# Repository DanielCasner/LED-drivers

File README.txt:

This repository contains source files for hardware software and simulation for various LED drivers initially created by Daniel Casner, www.danielcasner.org daniel@danielcasner.org

See LICENSE file for details on the licenses pertaining to various files.
Hardware source files are compatible with EAGLE 6.0 http://www.cadsoftusa.com/
Simulation source files are compatible with free LTSpice from Linear Technology http://www.linear.com/ltspice
There is no relationship nor implied endorcement between the author of this work and the above software tools.

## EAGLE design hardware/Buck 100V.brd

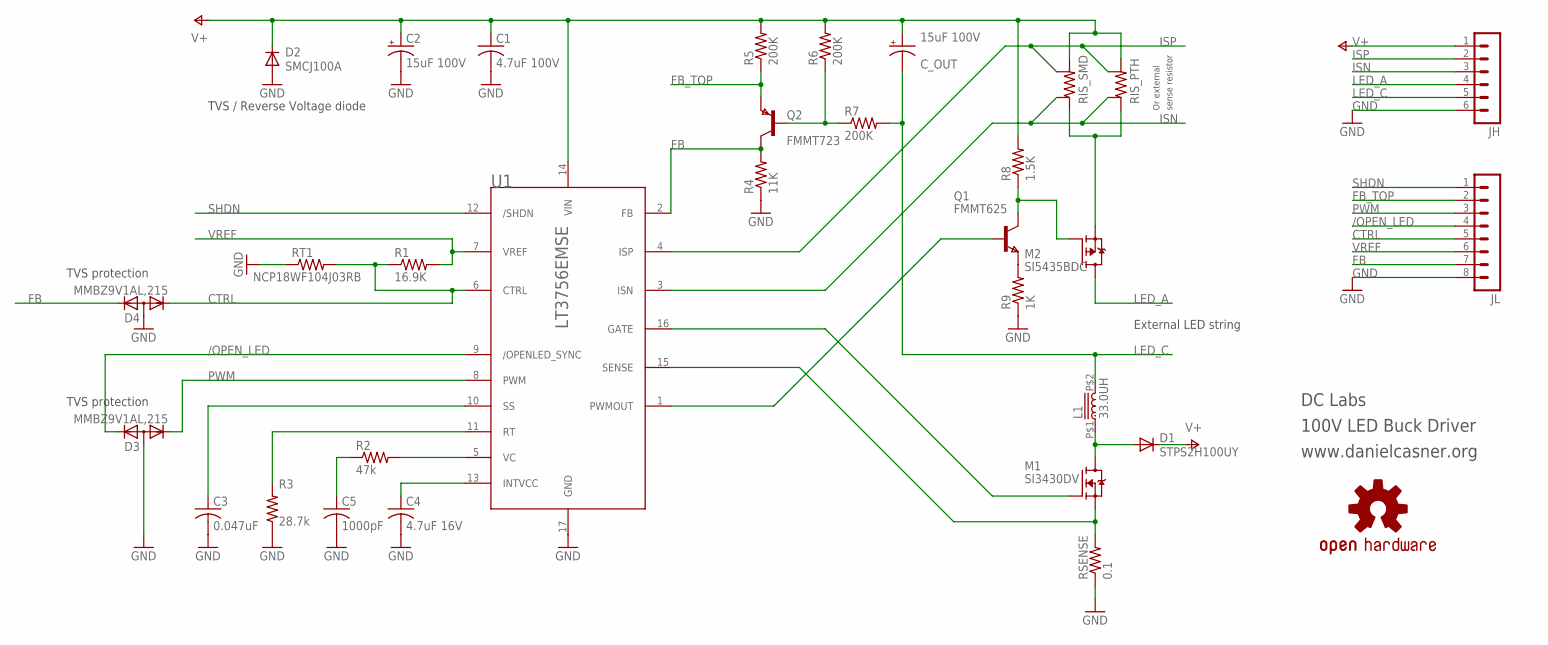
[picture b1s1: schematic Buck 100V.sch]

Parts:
C1: 4.7uF 100V; C2220K
C2: 15uF 100V; E2,5-6E
C3: 0.047uF; C0805
C4: 4.7uF 16V; C0805
C5: 1000pF; C0805
C_OUT: 15uF 100V; E2,5-6E
D1: STPS2H100UY; SMB
D2: SMCJ100A; SMC
D3, D4: MMBZ9V1AL,215; SOT23
JH: MA06-1
JL: MA08-1
L1: 33.0UH; ASPI-0612FS
M1: SI3430DV; SSOT6
M2: SI5435BDC; 1206-8CHIP-FET
Q1: FMMT625; SOT-23
Q2: FMMT723; SOT-23
R1: 16.9K; R0805
R2: 47k; R0805
R3: 28.7k; R0805
R4: 11K; R0805
R5, R6, R7: 200K; R0805
R8: 1.5K; R0805
R9: 1K; R0805
RIS_PTH: R-KELVIN0204/7; 0204/7-KELVIN
RIS_SMD: R-KELVINR2512; R2512_KELVIN
RSENSE: 0.1; R0805
RT1: NCP18WF104J03RB; R0805
U1: LT3756EMSE; MSOP16EXP
U$1: OSHW-LOGOS; OSHW-LOGO-S

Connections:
/OPEN_LED: D3.2 (K2), JL.4, U1.9 (/OPENLED_SYNC)
CTRL: D4.1 (K1), JL.5, R1.1, RT1.2, U1.6 (CTRL)
FB: D4.2 (K2), JL.7, Q2.1 (C), R4.2, U1.2 (FB)
FB_TOP: JL.2, Q2.2 (E), R5.1
GND: C1.2, C2.-, C3.2, C4.2, C5.2, D2.A, D3.3 (A), D4.3 (A), JH.6, JL.8, R3.1, R4.1, R9.1, RSENSE.1, RT1.1, U1.17 (GND)
ISN: JH.3, RIS_PTH.1S, RIS_SMD.1S, U1.3 (ISN)
ISP: JH.2, RIS_PTH.2S, RIS_SMD.2S, U1.4 (ISP)
LED_A: JH.4, M2.1 (D), M2.2 (D), M2.3 (D), M2.6 (D), M2.7 (D), M2.8 (D)
LED_C: C_OUT.-, JH.5, L1.P$2 (2), R7.2
unnamed: C3.1, U1.10 (SS)
unnamed: C4.1, U1.13 (INTVCC)
unnamed: R2.2, U1.5 (VC)
unnamed: C5.1, R2.1
unnamed: R3.2, U1.11 (RT)
unnamed: M2.5 (S), RIS_PTH.1, RIS_SMD.1
unnamed: Q2.3 (B), R6.1, R7.1
unnamed: M2.4 (G), Q1.1 (C), R8.1
unnamed: Q1.2 (E), R9.2
unnamed: Q1.3 (B), U1.1 (PWMOUT)
unnamed: M1.3 (G), U1.16 (GATE)
unnamed: M1.4 (S), RSENSE.2, U1.15 (SENSE)
N_BUCK: D1.A, L1.P$1 (1), M1.1 (D), M1.2 (D), M1.5 (D), M1.6 (D)
PWM: D3.1 (K1), JL.3, U1.8 (PWM)
SHDN: JL.1, U1.12 (/SHDN)
V+: C1.1, C2.+, C_OUT.+, D1.C, D2.C, JH.1, R5.2, R6.2, R8.2, RIS_PTH.2, RIS_SMD.2, U1.14 (VIN)
VREF: JL.6, R1.2, U1.7 (VREF)

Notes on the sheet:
TVS / Reverse Voltage diode
TVS protection
Or external
sense resistor
External LED string
DC Labs
100V LED Buck Driver
www.danielcasner.org

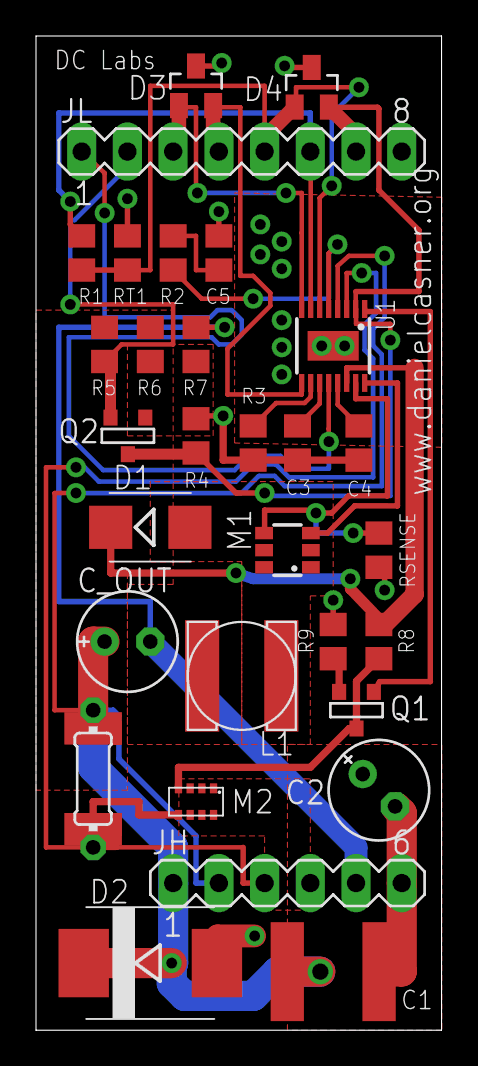
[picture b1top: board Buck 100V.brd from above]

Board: 2 copper layers, 22.5 x 55.2 mm, 32 parts (1 on the bottom side), 26 nets.

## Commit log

2012-03-02 Initialization commit
2012-03-02 Add simulation source files.
2012-03-03 Add license file, add content to readme file and rename to add .txt for windows users.
2012-03-03 Checkpoint, added EAGLE Library and start buck schematic.
2012-03-12 More progress on schematic.
2012-03-13 More work on Buck schematic. Now it just needs the schotkey diode, headers and double checking.
2012-03-14 Add schottky diode. Change resistors and caps to 0805 for hand solderability. Still need headers and checking before starting layout. Also need reverse protection diode and possibly est protection co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
2012-03-15 Finished schematic (needs a careful double check). Added LTSpice output files to .gitignore.
2012-03-15 Beautify and correct the schematic. Made the two headers different sizes so that it is harder to put the part in backwards. Next step is to run and confirm BOM.
2012-03-17 Minor fixes.
2012-03-17 Add BOM spread sheet for Buck driver.
2012-03-17 Add board created from schematic. No placement done yet.
2012-03-21 Create kelvin terminated versions of current sense resistors and adjust schematic accordingly. Signals on the buck headers are now more clearly named. The kelvin terminated resistors WILL cause DRC e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
2012-03-24 Very rough initial board layout. Can now safely say that the board will be smaller than 2 inches by 3 inches.
2012-04-07 Some progress on layout and routing.
2012-04-14 Progress on layout and routing.
2012-04-28 Checkpoint before trying autorouting again.
2012-04-28 VICTORY! Over place and route.
2012-04-29 Smash size and position part names for screen printing.
2012-04-29 Add DRC and CAM scripts, some modification to go with new DRC.
2012-05-02 Better routing for ESD protection. Fix airwires.
2012-05-02 Fine tune routing after reviewing gerbers.
2012-05-05 Add BatchPCB design rules and cam script. Make some adjustments to the layout for batchPCB rule check.
2012-05-06 Modify BatchPCB cam file to my tastes and their updated requirements. Add more silk screen labeling to the board. Update the BOM.
2012-05-10 Working on a library part to represent the led driver board on other boards.
2012-07-08 Finish library part of LED 100V buck driver for use in other boards.
2012-08-15 Add documentation
2012-08-15 Missed from previous commit.
2012-08-15 Added manufacturing files from 2012-05 build.
    Moved BOM into manufacturing folder.
2012-08-21 Add figure of 100V LED driver component.

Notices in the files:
parts and their libraries:
SparkFun-Aesthetics: Licensing: CC v3.0 Share-Alike You are welcome to use this library for commercial purposes.
